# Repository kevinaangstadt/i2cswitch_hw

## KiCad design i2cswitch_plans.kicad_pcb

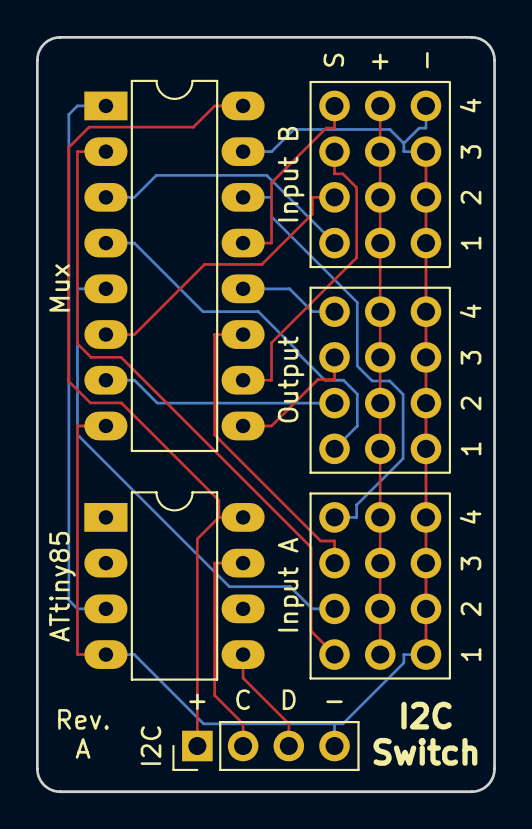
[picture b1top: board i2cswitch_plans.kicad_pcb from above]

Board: 2 copper layers, 25.4 x 41.9 mm, 6 parts (0 on the bottom side), 18 nets.

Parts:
ATtiny85: ATTINY85-P; DIP-8_W7.62mm_LongPads
I2C: KEVIN_01X04; Socket_Strip_Straight_1x04_Pitch2.54mm
Input A: CONN_03X04; Socket_Strip_Straight_3x04_Pitch2.54mm
Input B: CONN_03X04; Socket_Strip_Straight_3x04_Pitch2.54mm
Mux: 74HC157N; DIP-16_W7.62mm_LongPads
Output: CONN_03X04; Socket_Strip_Straight_3x04_Pitch2.54mm

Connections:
GND: ATtiny85.4, I2C.4, Input A.9, Input A.10, Input A.11, Input A.12, Input B.9, Input B.10, Input B.11, Input B.12, Mux.8, Mux.15, Output.9, Output.10, Output.11, Output.12
unnamed: ATtiny85.3, Mux.1
unnamed: Input A.2, Input A.4, Input A.6, Input A.8, Input B.2, Input B.4, Input B.6, Input B.8, Output.2, Output.4, Output.6, Output.8
SCL: ATtiny85.7, I2C.2
SD: ATtiny85.5, I2C.3
VCC: ATtiny85.8, I2C.1, Mux.16
in1a: Input A.1, Mux.2
in1b: Input B.1, Mux.3
in2a: Input A.3, Mux.5
in2b: Input B.3, Mux.6
in3a: Input A.5, Mux.11
in3b: Input B.5, Mux.10
in4a: Input A.7, Mux.14
in4b: Input B.7, Mux.13
out1: Mux.4, Output.1
out2: Mux.7, Output.3
out3: Mux.9, Output.5
out4: Mux.12, Output.7
